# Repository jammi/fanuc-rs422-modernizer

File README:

This is an adapter board (WIP) for bridging modern RX/TX/GND -serial to the differential layout used by vintage Fanuc CNC machines' remote buffer interfaces.

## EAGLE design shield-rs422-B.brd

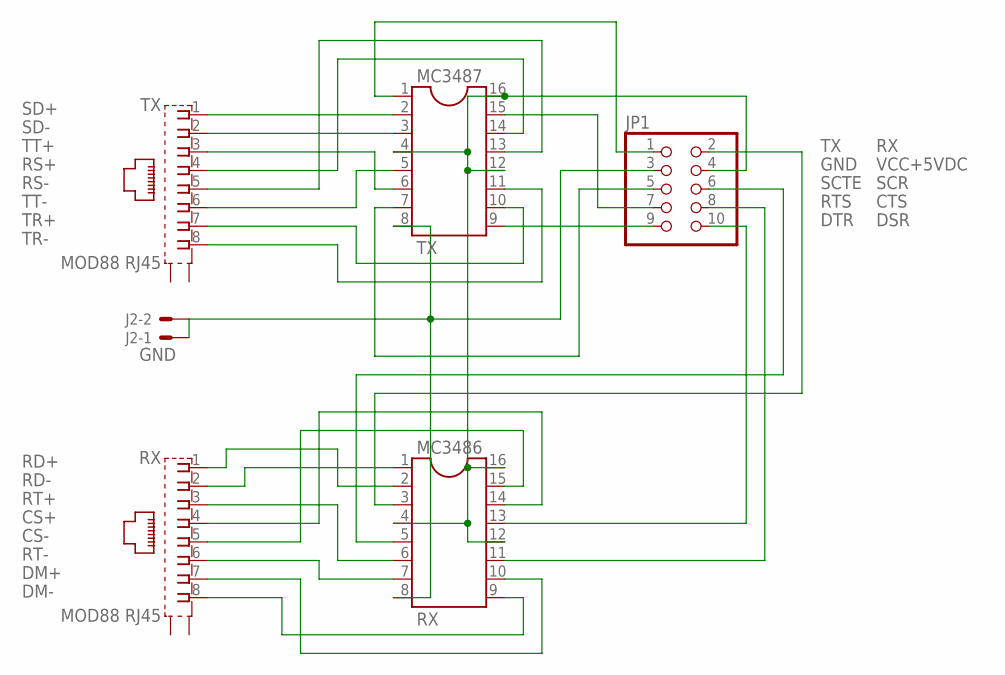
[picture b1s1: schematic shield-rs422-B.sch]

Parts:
J2: GND; 7395-02
JP1: PINHD-2X5/90; 2X05/90
MC3486: RX; DIL16
MC3487: TX; DIL16
RX: MOD88 RJ45; GLX-S-88M
TX: MOD88 RJ45; GLX-S-88M

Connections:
CS+: MC3486.14, RX.4
CS-: MC3486.15, RX.5
CTS: JP1.8, MC3486.11
DM+: MC3486.10, RX.7
DM-: MC3486.9, RX.8
DSR: JP1.10, MC3486.13
DTR: JP1.9, MC3487.9
GND: J2.1, J2.2, JP1.3, MC3486.8, MC3487.8
RD+: MC3486.2, RX.1
RD-: MC3486.1, RX.2
RS+: MC3487.14, TX.4
RS-: MC3487.13, TX.5
RT+: MC3486.6, RX.3
RT-: MC3486.7, RX.6
RTS: JP1.7, MC3487.15
RX: JP1.2, MC3486.3
SCR: JP1.6, MC3486.5
SCTE: JP1.5, MC3487.7
SD+: MC3487.2, TX.1
SD-: MC3487.3, TX.2
TR+: MC3487.10, TX.7
TR-: MC3487.11, TX.8
TT+: MC3487.6, TX.3
TT-: MC3487.5, TX.6
TX: JP1.1, MC3487.1
VCC+5VDC: JP1.4, MC3486.4, MC3486.12, MC3486.16, MC3487.4, MC3487.12, MC3487.16

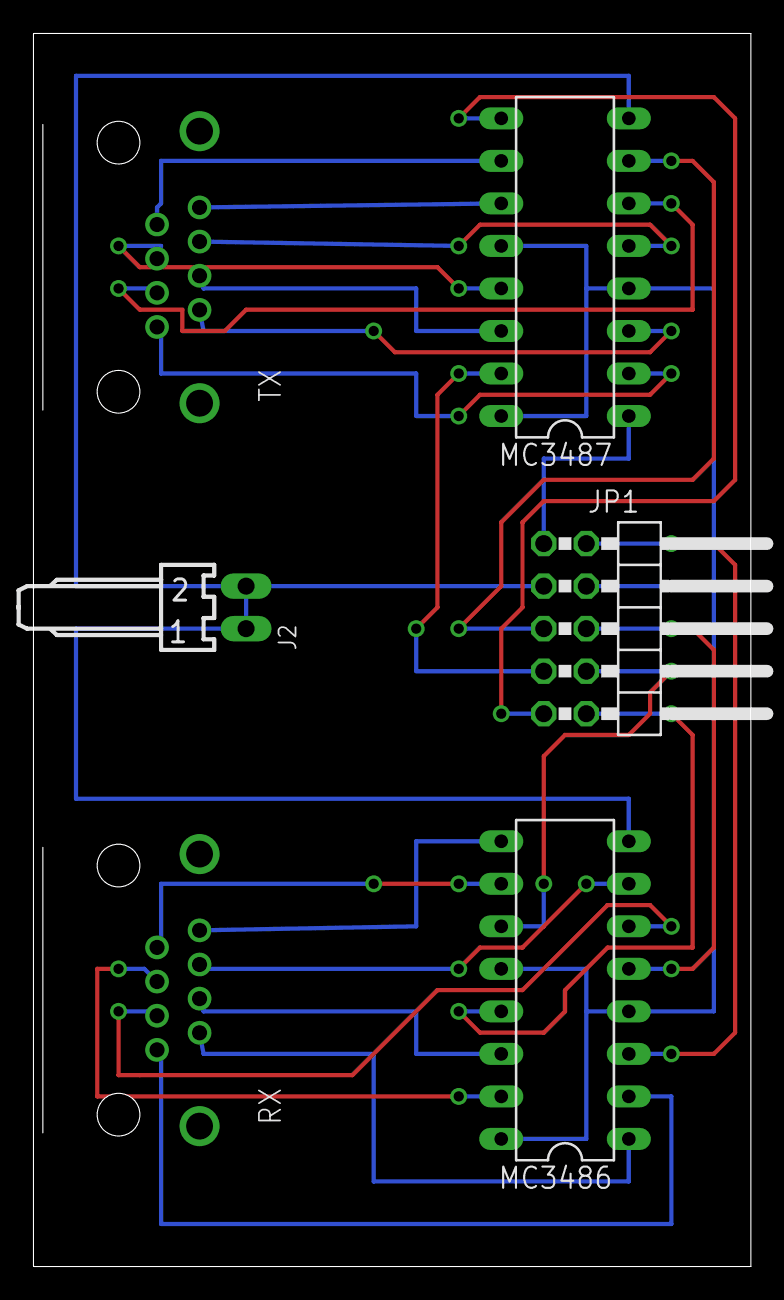
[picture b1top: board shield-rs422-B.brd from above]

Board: 2 copper layers, 42.8 x 73.7 mm, 6 parts (0 on the bottom side), 26 nets.

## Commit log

2015-12-12 initial commit of differential send/receive adapter for use between the fanuc series 0 rs422 interface and a modern serial interface, like gpio-based connections to raspberries, arduinos and so forth
2015-12-13 variant B of the board, designed for perfboard
2015-12-15 Basic LICENSE and README, nothing's changed, just the defaults of the preject regarding copyright.
